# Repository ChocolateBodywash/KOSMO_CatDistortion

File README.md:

## KOSMO Format Cat Distortion 

A KOSMO format of a PROCO Rat distortion pedal.

I love the PROCO RAT Distortion, so I adapted it for Synth DIY.

I’ve always loved the RAT, so I reworked it for Synth DIY. If you want the deep dive into how the circuit works, check out this excellent breakdown:
https://www.electrosmash.com/proco-rat

For this version, I swapped the original op-amp for a more common TL072. The clipping circuit also got an upgrade, the diodes were replaced with LEDs, which double as glowing cat eyes on the panel. They're actually part of the circuit, not just for show. Different colours will have different forward voltages and thus may effect the sound (although I haven't tested this).

The front panel design was created using JLCPCB's colour silkscreen option, which is only avalible with easyEDA. My Kicad files are just one static colour.

Note: Because I'm not entirely sure what I'm doing, the maximum output level might be a bit much. This has a useful side effect though, it can bring guitar level to synth level.

---
Note: This was created by a hobbyist with no formal engineering training outside various late night YouTube binges. 
I’ve confirmed these designs to work but I make no guarantees on the design working efficiently.. or working at all.

Additional credit: Analog Output (Richard Holmes) for footprint libraries and front panel templates.

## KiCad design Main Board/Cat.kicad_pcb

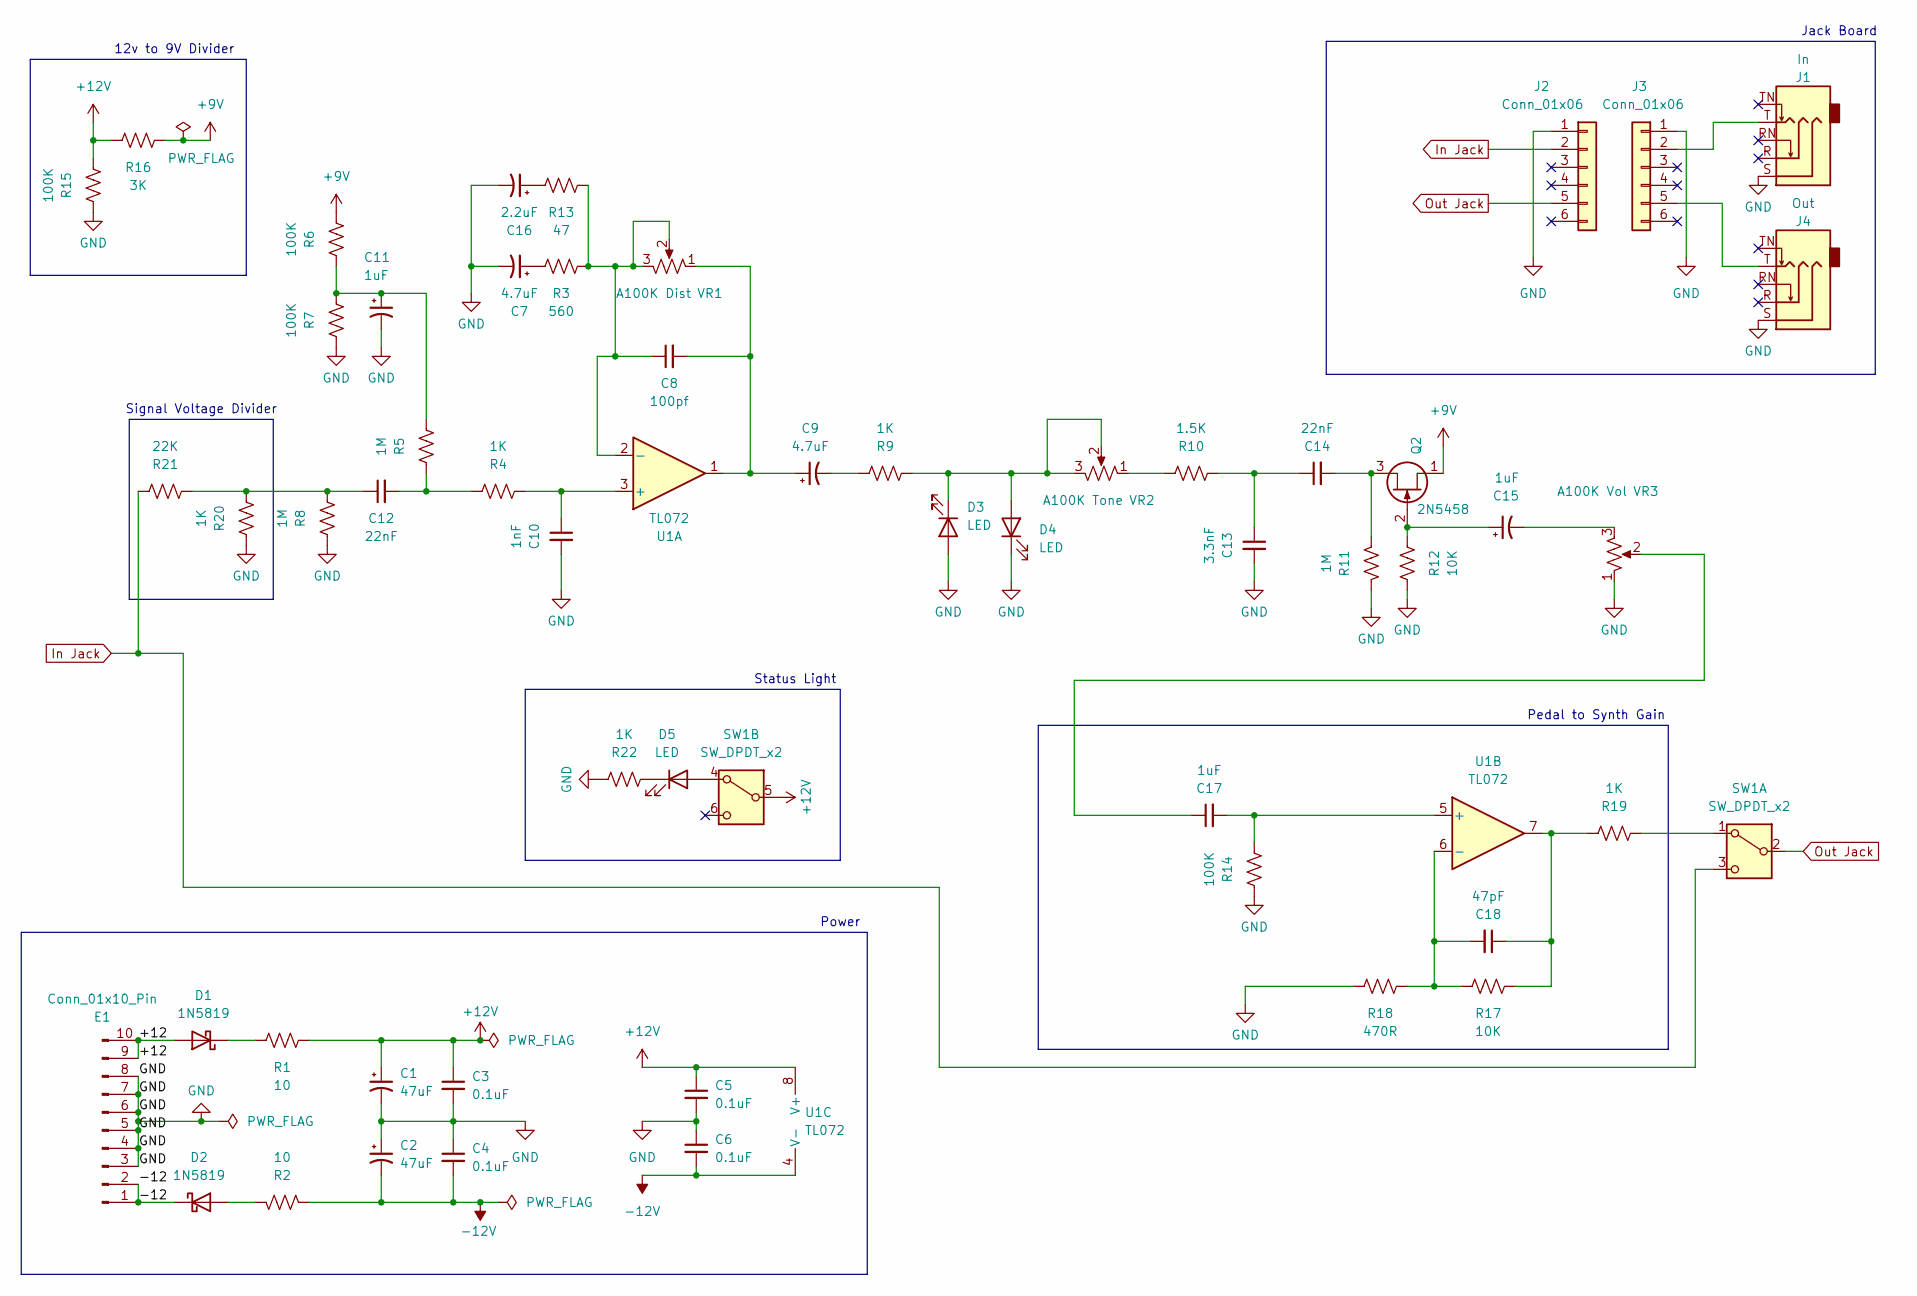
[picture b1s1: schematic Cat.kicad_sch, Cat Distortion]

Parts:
C1, C2: 47uF; CP_Radial_D5.0mm_P2.50mm
C3, C4, C5, C6: 0.1uF; C_Disc_D3.0mm_W1.6mm_P2.50mm
C7, C9: 4.7uF; CP_Radial_D5.0mm_P2.50mm
C8: 100pf; C_Disc_D3.0mm_W1.6mm_P2.50mm
C10: 1nF; C_Rect_L7.2mm_W2.5mm_P5.00mm_FKS2_FKP2_MKS2_MKP2
C11, C15: 1uF; CP_Radial_D5.0mm_P2.50mm
C12, C14: 22nF; C_Rect_L7.2mm_W2.5mm_P5.00mm_FKS2_FKP2_MKS2_MKP2
C13: 3.3nF; C_Rect_L7.2mm_W2.5mm_P5.00mm_FKS2_FKP2_MKS2_MKP2
C16: 2.2uF; CP_Radial_D5.0mm_P2.50mm
C17: 1uF; C_Rect_L7.2mm_W2.5mm_P5.00mm_FKS2_FKP2_MKS2_MKP2
C18: 47pF; C_Disc_D3.0mm_W1.6mm_P2.50mm
D1, D2: 1N5819; D_DO-41_SOD81_P10.16mm_Horizontal
D3, D4, D5: LED; LED_D5.0mm
E1: Conn_01x10_Pin; Pins_2x05_2.54mm_TH_EurorackPower_Shrouded
J1: In; Jack_6.35mm_PJ_629HAN
J2, J3: Conn_01x06; PinHeader_1x06_P2.54mm_Vertical_Centre
J4: Out; Jack_6.35mm_PJ_629HAN
Q2: 2N5458; TO-92L_Inline_Wide
R1, R2: 10; R_Axial_DIN0207_L6.3mm_D2.5mm_P10.16mm_Horizontal
R3: 560; R_Axial_DIN0207_L6.3mm_D2.5mm_P10.16mm_Horizontal
R4, R9, R19, R20, R22: 1K; R_Axial_DIN0207_L6.3mm_D2.5mm_P10.16mm_Horizontal
R5, R8, R11: 1M; R_Axial_DIN0207_L6.3mm_D2.5mm_P10.16mm_Horizontal
R6, R7, R14, R15: 100K; R_Axial_DIN0207_L6.3mm_D2.5mm_P10.16mm_Horizontal
R10: 1.5K; R_Axial_DIN0207_L6.3mm_D2.5mm_P10.16mm_Horizontal
R12, R17: 10K; R_Axial_DIN0207_L6.3mm_D2.5mm_P10.16mm_Horizontal
R13: 47; R_Axial_DIN0207_L6.3mm_D2.5mm_P10.16mm_Horizontal
R16: 3K; R_Axial_DIN0207_L6.3mm_D2.5mm_P10.16mm_Horizontal
R18: 470R; R_Axial_DIN0207_L6.3mm_D2.5mm_P10.16mm_Horizontal
R21: 22K; R_Axial_DIN0207_L6.3mm_D2.5mm_P10.16mm_Horizontal
SW1: SW_DPDT_x2; DPDT-toggle-switch-1M-seriesx
U1: TL072; DIP-8_W7.62mm_Socket_LongPads
VR1: A100K Dist; Potentiometer_Alpha_RD901F-40-00D_Single_Vertical
VR2: A100K Tone; Potentiometer_Alpha_RD901F-40-00D_Single_Vertical
VR3: A100K Vol; Potentiometer_Alpha_RD901F-40-00D_Single_Vertical

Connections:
+9V: Q2.1 (D), R6.1, R16.2
+12V: C1.1, C3.1, C5.1, R1.2, R15.1, R16.1, SW1.5 (B), U1.8 (V+)
-12V: C2.2, C4.2, C6.2, R2.2, U1.4 (V-)
/+12: D1.2 (A), E1.9, E1.10
/-12: D2.1 (K), E1.1, E1.2
GND: C1.2, C2.1, C3.2, C4.1, C5.2, C6.1, C7.2, C10.2, C11.2, C13.2, C16.2, D3.2 (A), D4.1 (K), E1.3, E1.4, E1.5, E1.6, E1.7, E1.8, J1.S, J2.1, J3.1, J4.S, R7.2, R8.2, R11.1, R12.1, R14.2, R15.2, R18.1, R20.2, R22.2, VR3.1
In Jack: J2.2, R21.2, SW1.3 (C)
unnamed: C7.1, R3.1
unnamed: C8.2, C9.1, U1.1, VR1.1
unnamed: C9.2, R9.2
unnamed: C11.1, R5.1, R6.2, R7.1
unnamed: C12.1, R8.1, R20.1, R21.1
unnamed: C12.2, R4.2, R5.2
unnamed: C13.1, C14.1, R10.1
unnamed: C15.2, VR3.3
unnamed: C16.1, R13.1
unnamed: C17.1, VR3.2
unnamed: C18.1, R17.2, R19.2, U1.7
unnamed: D1.1 (K), R1.1
unnamed: D2.2 (A), R2.1
unnamed: D3.1 (K), D4.2 (A), R9.1, VR2.2, VR2.3
unnamed: D5.2 (A), SW1.4 (A)
unnamed: D5.1 (K), R22.1
unnamed: J1.T, J3.2
unnamed: J3.5, J4.T
unnamed: C15.1, Q2.2 (G), R12.2
unnamed: C14.2, Q2.3 (S), R11.2
unnamed: R10.2, VR2.1
unnamed: R19.1, SW1.1 (A)
unnamed: C10.1, R4.1, U1.3 (+)
unnamed: C8.1, R3.2, R13.2, U1.2 (-), VR1.2, VR1.3
unnamed: C17.2, R14.1, U1.5 (+)
unnamed: C18.2, R17.1, R18.2, U1.6 (-)
Out Jack: J2.5, SW1.2 (B)

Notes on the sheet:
Pedal to Synth Gain
12v to 9V Divider
Status Light
Signal Voltage Divider
Jack Board
Power

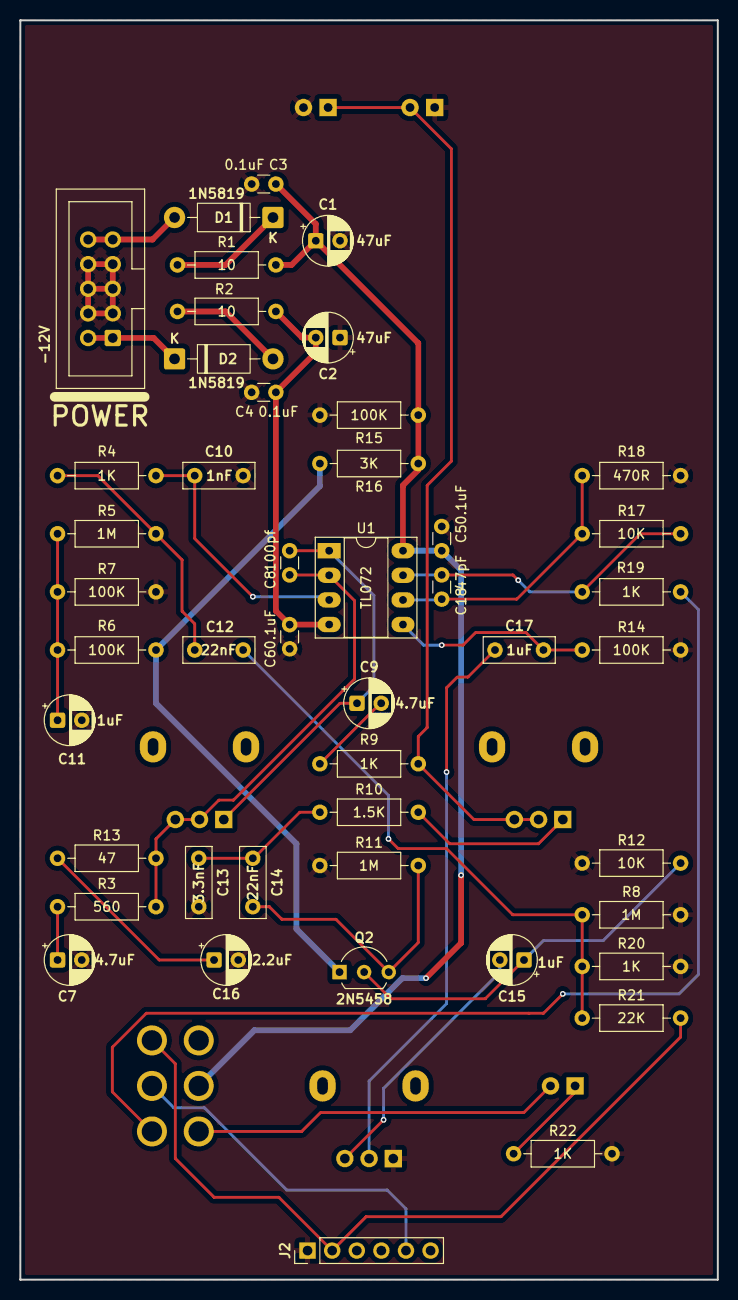
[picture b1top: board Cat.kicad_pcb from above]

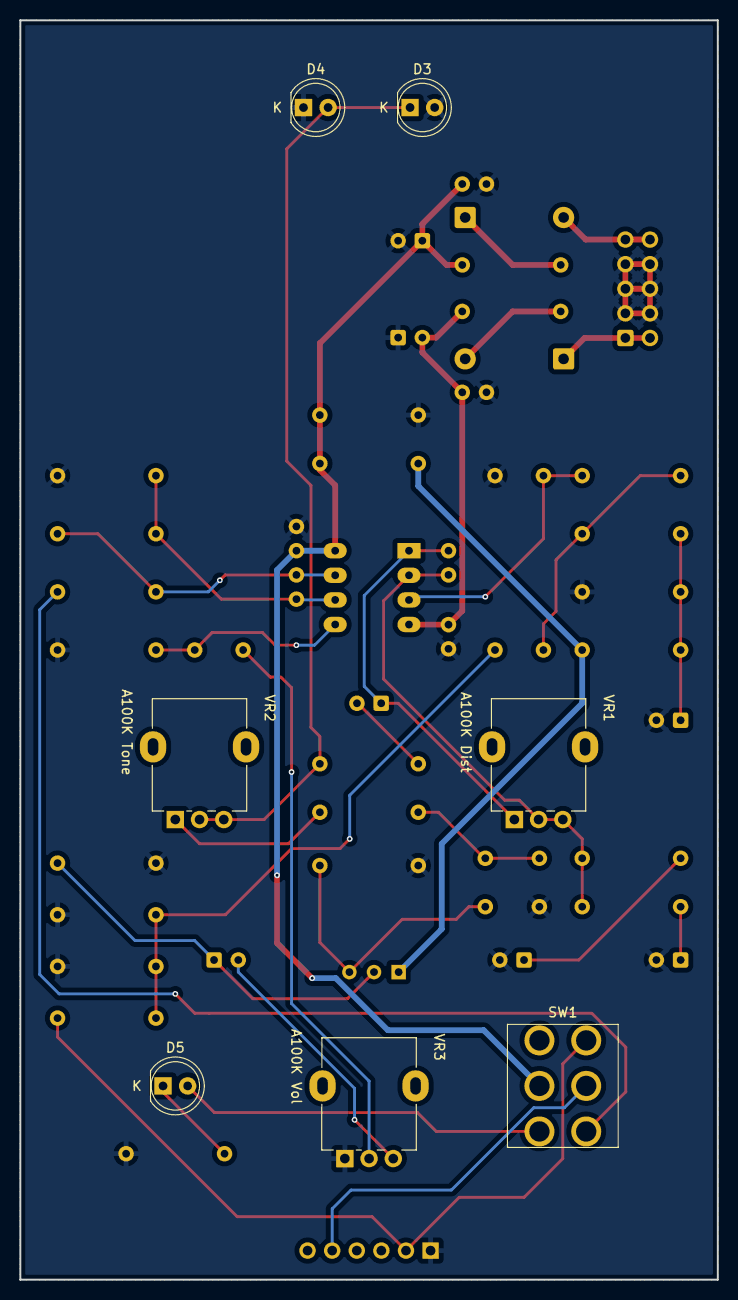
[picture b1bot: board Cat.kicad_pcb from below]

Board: 2 copper layers, 72.0 x 130.0 mm, 53 parts (7 on the bottom side), 32 nets.

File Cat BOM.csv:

Reference,Value,Datasheet,Package,Qty
"C1,C2",47uF,~,Electrolytic Capacitor,2
"C3,C4,C5,C6",0.1uF,~,Ceramic Disc Capacitor,4
"C7,C9",4.7uF,~,Electrolytic Capacitor,2
C8,100pf,~,Ceramic Disc Capacitor,1
C10,1nF,~,Box Style Film Capacitor,1
"C11,C15",1uF,~,Electrolytic Capacitor,3
C17,1uF,~,Box Style Film Capacitor,
"C12,C14",22nF,~,Box Style Film Capacitor,2
C13,3.3nF,~,Box Style Film Capacitor,1
C16,2.2uF,~,Electrolytic Capacitor,1
C18,47pF,~,Ceramic Disc Capacitor,1
"D1,D2",1N5819,http://www.vishay.com/docs/88525/1n5817.pdf,Diode_THT:D_DO-41_SOD81_P10.16mm_Horizontal,2
"D3,D4,D5",LED,~,LED 5.0mm (I used green for the eyes. These are part of the cliping stage different colours may have different effects),3
E1,Conn_02x05_Pin,~,Pins_2x05_2.54mm_TH_EurorackPower_Shrouded,1
J1,In,~,Jack_6.35mm,1
"J2,J3",Conn_01x06,~,Connector_PinHeader_2.54mm:PinHeader_1x06_P2.54mm_Vertical,2
J4,Out,~,Jack_6.35mm,1
Q2,2N5458,https://my.centralsemi.com/datasheets/2N3819.PDF,Package_TO_SOT_THT:TO-92L_Inline_Wide,1
"R1,R2",10,~,Metal Film 1/4 Resistor,2
R3,560,~,Metal Film 1/4 Resistor,1
"R4,R9,R19,R20,R22",1K,~,Metal Film 1/4 Resistor,5
"R5,R8,R11",1M,~,Metal Film 1/4 Resistor,3
"R6,R7,R14,R15",100K,~,Metal Film 1/4 Resistor,4
R10,1.5K,~,Metal Film 1/4 Resistor,1
"R12,R17",10K,~,Metal Film 1/4 Resistor,2
R13,47,~,Metal Film 1/4 Resistor,1
R16,3K,~,Metal Film 1/4 Resistor,1
R18,470R,~,Metal Film 1/4 Resistor,1
R21,22K,~,Metal Film 1/4 Resistor,1
SW1,SW_DPDT_x2,~,DPDT switch,1
U1,TL072,http://www.ti.com/lit/ds/symlink/tl071.pdf,DIP-8_W7.62mm,1
VR1,A100K Dist,~,Potentiometer_Alpha_RD901F-40-00D_Single_Vertical,1
VR2,A100K Tone,~,Potentiometer_Alpha_RD901F-40-00D_Single_Vertical,1
VR3,A100K Vol,~,Potentiometer_Alpha_RD901F-40-00D_Single_Vertical,1

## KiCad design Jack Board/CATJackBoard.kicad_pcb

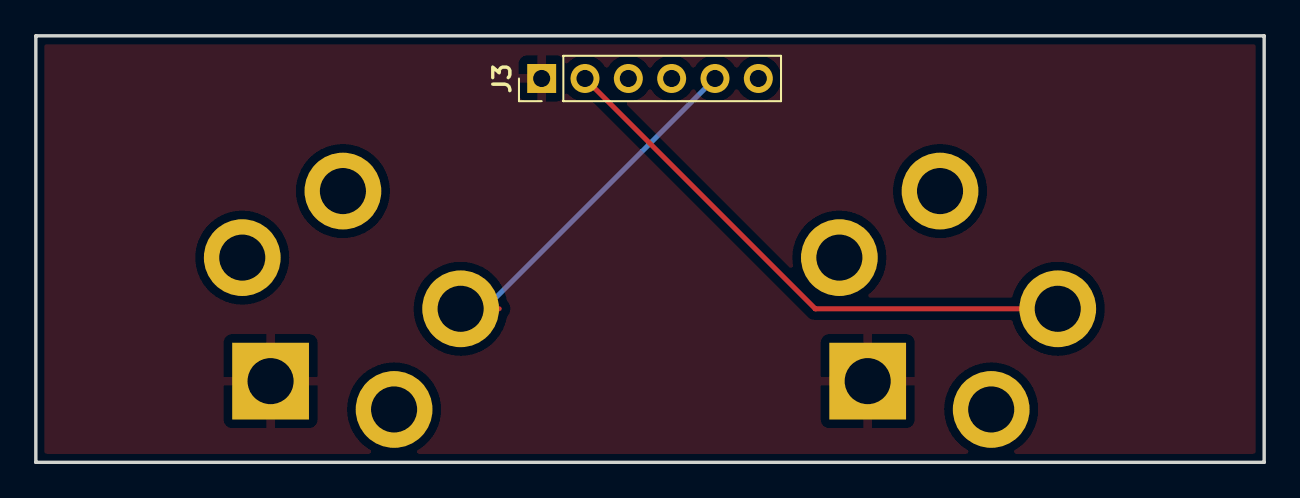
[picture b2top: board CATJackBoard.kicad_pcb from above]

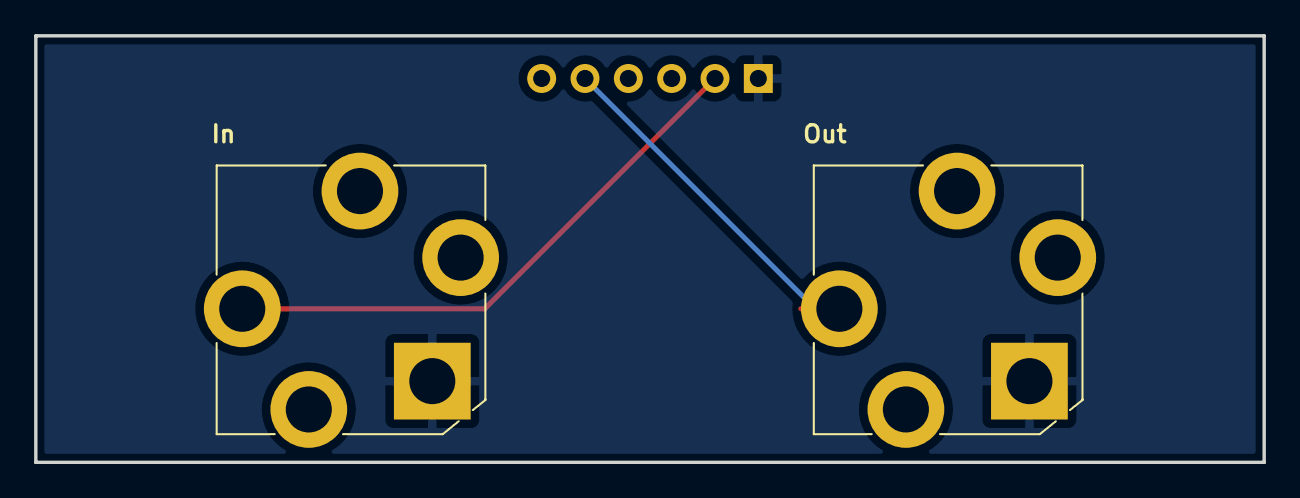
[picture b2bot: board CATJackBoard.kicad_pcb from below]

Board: 2 copper layers, 72.0 x 25.0 mm, 3 parts (2 on the bottom side), 3 nets.

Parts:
J1: In; Jack_6.35mm_PJ_629HAN
J3: Conn_01x06; PinHeader_1x06_P2.54mm_Vertical
J4: Out; Jack_6.35mm_PJ_629HAN

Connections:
GND: J1.S, J3.1, J4.S
unnamed: J1.T, J3.2
unnamed: J3.5, J4.T

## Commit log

2025-10-24 Upload files
2025-10-27 Update image
2025-10-29 Upload Schematics
